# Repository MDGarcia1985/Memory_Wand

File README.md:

<!--
Author: Michael Garcia, M&E Design
License: MIT
Date: 2026-04-17
Contact: michael@mandedesign.studio
Website: https://mandedesign.studio
-->

# Memory Wand

Memory Wand is a modular embedded firmware project for a light-and-sound memory toy.

## Repository Role

This repository contains:

- Firmware modules for input, event processing, LED output, and audio output
- Board pin and behavior configuration
- A simple audio data pipeline for generated sound definitions
- Supporting project documentation for architecture, coding standards, and commenting policy

## Architecture Summary

The firmware follows a non-blocking event-driven flow:

`button GPIO -> debounce -> button events -> event queue -> tasks -> LED/audio outputs`

That separation is intentional so the project can evolve without tightly coupling hardware details to gameplay behavior.

## Core Directories

- `include/`: Public project headers and subsystem contracts
- `src/`: Runtime implementations and firmware entry point
- `include/audio/` and `src/audio/`: Audio abstraction, generated data access, and platform drivers
- `include/drivers/` and `src/drivers/`: Hardware-facing output drivers
- `lib/ButtonDebounce/`: Vendored button debounce dependency used by the input wrapper
- `audio_builder/`: Source data and scripts for generated sound content
- `docs/`: Architecture, standards, and development notes
- `archive/`: Older experimental or reference code

## Build

This project uses PlatformIO.

```bash
platformio run
```

## Versioning

The repository version is tracked in the root `VERSION` file.

Releases follow semantic versioning:

- Major: incompatible architectural or API changes
- Minor: new features added in a backward-compatible way
- Patch: fixes and non-breaking cleanup

The current major release line is defined by the first number in `VERSION`.

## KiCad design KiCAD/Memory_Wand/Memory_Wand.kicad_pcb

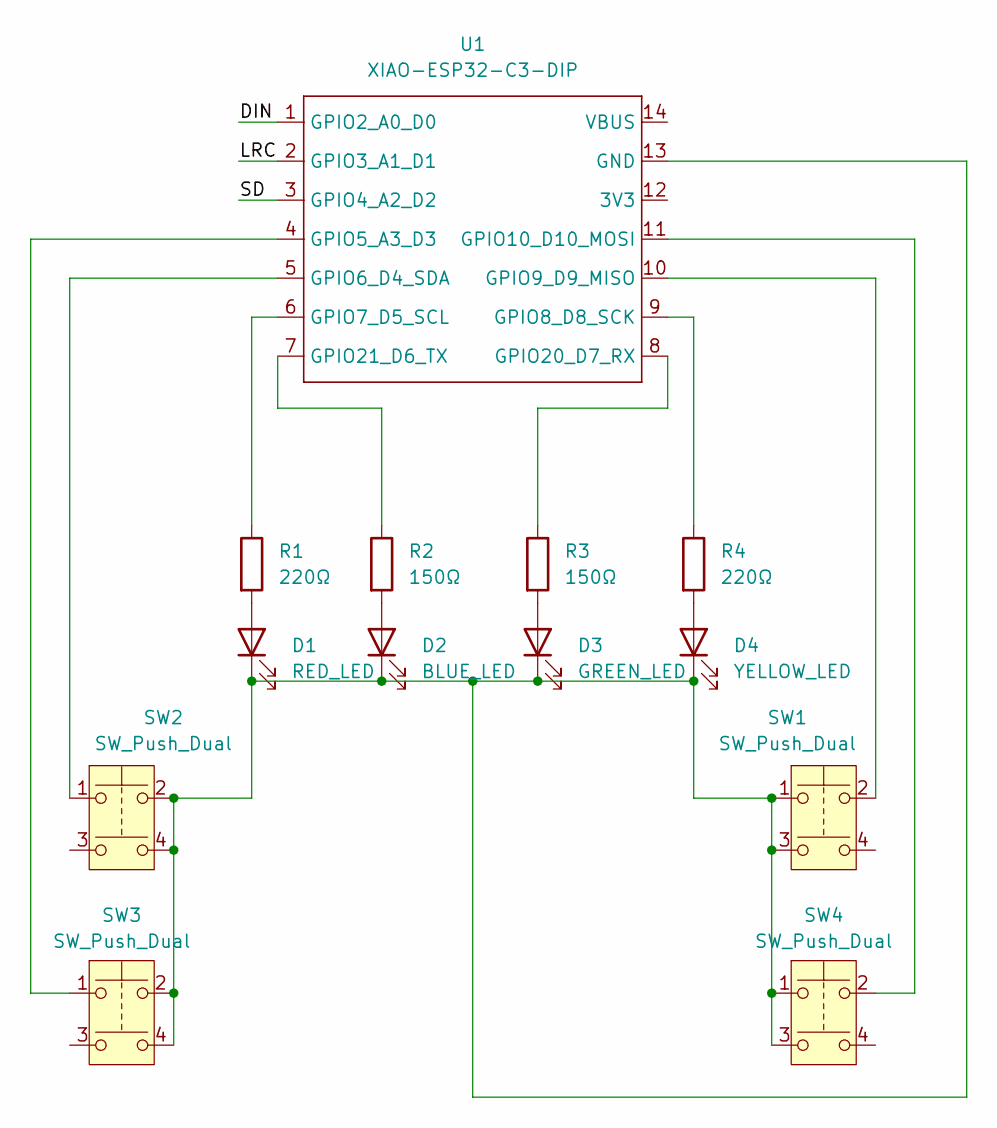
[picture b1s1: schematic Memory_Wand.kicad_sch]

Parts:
D1: RED_LED; LED_D5.0mm
D2: BLUE_LED; LED_D5.0mm
D3: GREEN_LED; LED_D5.0mm
D4: YELLOW_LED; LED_D5.0mm
R1, R4: 220Ω; R_Axial_DIN0309_L9.0mm_D3.2mm_P12.70mm_Horizontal
R2, R3: 150Ω; R_Axial_DIN0309_L9.0mm_D3.2mm_P12.70mm_Horizontal
SW1, SW2, SW3, SW4: SW_Push_Dual; Push_E-Switch_KS01Q01
U1: XIAO-ESP32-C3-DIP; MCU_Seeed_ESP32C3

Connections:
/DIN: U1.1 (GPIO2_A0_D0)
/LRC: U1.2 (GPIO3_A1_D1)
/SD: U1.3 (GPIO4_A2_D2)
unnamed: D1.2 (A), R1.2
unnamed: D1.1 (K), D2.1 (K), D3.1 (K), D4.1 (K), SW1.1, SW1.3, SW2.2, SW2.4, SW3.2, SW3.4, SW4.1, SW4.3, U1.13 (GND)
unnamed: D2.2 (A), R2.2
unnamed: D3.2 (A), R3.2
unnamed: D4.2 (A), R4.2
unnamed: SW3.1, U1.4 (GPIO5_A3_D3)
unnamed: SW2.1, U1.5 (GPIO6_D4_SDA)
unnamed: R1.1, U1.6 (GPIO7_D5_SCL)
unnamed: R4.1, U1.9 (GPIO8_D8_SCK)
unnamed: SW1.2, U1.10 (GPIO9_D9_MISO)
unnamed: SW4.2, U1.11 (GPIO10_D10_MOSI)
unnamed: R3.1, U1.8 (GPIO20_D7_RX)
unnamed: R2.1, U1.7 (GPIO21_D6_TX)

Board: 2 copper layers, 13 parts (1 on the bottom side), 13 nets, no tracks yet.

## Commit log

2026-04-17 Initial commit
    Changes to be committed:
    new file: .gitignore
    new file: .vscode/extensions.json
    new file: KiCAD/Memory_Wand/Memory_Wand-backups/Memory_Wand-2026-02-16_193859.zip
    new file: KiCAD/Memory_Wand/Memory_Wand-backups/Memory_Wand-2026-02-16_200450.zip
    new file: KiCAD/Memory_Wand/Memory_Wand-backups/Memory_Wand-2026-02-16_201838.zip
2026-04-18 Major Version Released 2026-04-17 Changes to be committed: modified: .gitignore new file: LICENSE new file: README.md new file: VERSION modified: archive/demo_main.cpp new file: audio_builder/data/me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
2026-04-22 Chore: Debugged the tinkerCAD sketch. Program works for Arduino breadboard prototypes. Changes to be committed: modified: archive/demo_main.cpp
